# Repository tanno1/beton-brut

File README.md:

### beton brut
### noah tanner
### summer 2024

beton brut is a brutalist inspired, 66pc keyboard based on the Leopold FC660M layout complete with a concrete case designed from scratch and built by noah tanner.
this readme file will outline the design and build process, while highlighting technical details in a way that hopefully is not too boring. if i do this all correctly, this document should be guiding and inspiring enough for people to embark on their own rewarding journey of making a keyboard from scratch (it is so satisfying typing this document on my own keyboard).

#### table of contents
1. [preliminary-design](#preliminary-design)
2. [electronics](#electronics)
3. [firmware](#firmware)
4. [case](#case)
5. [other-items](#other-items)
7. [build](#build)
8. [reflection](#reflection)
9. [license](#license)
10. [acknowledgements](#acknowledegments)

### preliminary-design
the motivation for this project was enhance my electronics and product design skills by designing an aesthetic keyboard that pulled visual influence from 1950s [brutalist](https://en.wikipedia.org/wiki/Brutalist_architecture) architecture. starting with youtube videos and some internet browsing, i was able to breakdown the keyboard build process into a few parts: electronics, case, keys, and then the inbetween "joinery" stuff like gaskets and peripheral items to secure the pcb in the case. i have a background in mechanical engineering so i was familiar with micro controllers and electronics, but i had not designed a pcb before so i knew that would be the most difficult part of the project. 

for the keyboard design and layout, i went on keyboard layout editor ([kle](http://www.keyboard-layout-editor.com/())) and searched through default layouts. i was really hooked by the layout of the leopold fc660 with the two offset keys and the compact layout wihtout sacrificing the arrow keys. since it was going to be my first full custom pcb, i decided to move forward with the leopold layout rather than trying to create a new one for myself. as for the look of the case, i wanted it to be a simple slab of concrete, very minimally finished and decorated in order to align with the principles of brtualism. i chose a 6 degree angle to keep the case relatively flat, but still offer me some angle to align with my natural wrist positioning.

### electronics
i used kicad for pcb design. it is a great product and extremely easy to get familiar with. for the first iteration, i referenced a [video](https://www.youtube.com/watch?v=iznKltVU1yw) by noah kiser on youtube that showed the process of creating a keyboard pcb that used a teensy microcontroller unit and through hole diodes. noah detailed all of the footprints that would be used in keyboard making and where to find them online which was really helpful. that guide worked great up until the point where i started routing my martrix to the teensy and realized that the 18 gpio pinouts on the teensy were not enough to meet my 20 needed (5 rows and 15 columns). a quick reddit post about my dilemma and a few hour wait brought me into contact with markus knutsson ([github](https://github.com/TweetyDaBird/)). markus recommended that i alter my matrix layout in a way that would work, but would be quite ugly, or alternatively replace the teensy with an rp2040. from the start of the project, i was aware of using an on board mcu, but i was too nervous to setup the peripheral devices and risk messing it up. after reading marcus' reply, i checked online about the rp2040 mcu and decided to give it a try. having used raspberry pi devices in the past, i know their documentation is great, and that proved to be the case with the rp2040 as well. the [datasheet](https://datasheets.raspberrypi.com/rp2040/rp2040-datasheet.pdf?_gl=1*18x0kee*_ga*MTU3NjQ0Mzc0Ny4xNzI0NTQ0NTU5*_ga_22FD70LWDS*MTcyNDU0NDU1OS4xLjEuMTcyNDU0NDU4MC4wLjAuMA..) and the [hardware-design-with-the-rp2040](https://datasheets.raspberrypi.com/rp2040/hardware-design-with-rp2040.pdf?_gl=1*18x0kee*_ga*MTU3NjQ0Mzc0Ny4xNzI0NTQ0NTU5*_ga_22FD70LWDS*MTcyNDU0NDU1OS4xLjEuMTcyNDU0NDU4MC4wLjAuMA..) were all i needed to set up the rp2040 on my pcb. the hardware design manual had a very well written out process for setting up the rp2040 with qpsi flash storage, a usb port, a crystal, and information on sizing capacitors and resistors as well. thank you so much raspberry pi for making a datasheet that 1. doesn't suck, and 2. is't boring to read. 

after reading through these two manuals and with a few hours of work i was able to setup my first iteration of the pcb board. i was pretty hyped. i sent it over to marcus to get some feedback and he let me know that it was pretty terrible and problematic. the problems came in two forms. the first was that i routed every line to the outsides of the board, thinking that it would make sense to keep things away from the center and not crowd the board. while this worked out for the crwoding issue, it was a terrible design choice. routing traces to the edges of a board is bad for electromagnetic interference and could lead to issues with other electronics on my desk near the keyboard. the second issue with the board was that i did not use any vias. my reasoning for this came down to a lack of experience and pcb familiarity. i thought vias were a last resort thing and justified that, if i can put everything on one side, why not do that? inversely though, why not divide things on both sides of the board using vias and route N->S one side, and E->W on the other. 

building off the feedback from marcus, i started over from scratch and rerouted the whole board. as you can see in the photos, it looks so much better than the first iteration. routing across the two sides was way quicker than the first time thanks to the use of vias. after routing, i ran the kicad design rule checker (drc) and found a comically high number of warnings, 188 to be exact. luckily there were 0 errors, and the warnings were all about silkscreen overlaps. at this point i was just tidying up the loose ends. i fixed the silkscreen overlaps by moving the silkscreened component names around on the board and added a border for the board production. the 3d model looked great now, no errors, and marcus verified everything looked correct and was ready for production. 

i ordered everything off of jlpcb, and this was esaily the most confusing part of the project. jlpcb makes it really easy to go through the steps of uploading the files that you need like the gerbers, positioning, and bom. despite this, the component selection was difficult to navigate and find what piece you needed. i ended up having to reorder this a few times and ran into some errors of footprint sizing which meant i had to go back into kicad, select new footprints, and then re-export the gerbers again. luckily, the jlpcb staff is incredibly helpful and always avaiable online. no joke, they have a nigh shift team so any question i had, i would ask in the live chat and have a response in minutes. 

that wraps up the electronics.

### firmware
shoutout to [qmk](https://qmk.fm/). without them, this would not be possible. qmk makes the firmware sooo much easier, and they have extensive support for many mcus, including the rp2040. going through the qmk setup is pretty straightforward and i won't dive into it too much because i am not an expert on it. the main issue i had with qmk was the lack of documentation they had for their new config.json file. the setup through the config.json file is supposed to make the keyboard setup easier than it previously was. unfortunately, there is not a lot of good documentation about the config.json file itself and the current tutorial setup referes to the rules.mk file and the "old" way of doing things, so it got a bit tricky to navigate. regardless, the cli tool and qmk firmware as a whole are incredible projects and i cannot wait to work more with them in future keyboards. 

### case
to design the case, i needed to finalize the pcb to have information on the dimensions to build around. sticking to my original design, i made a really simple slab case in fusion 360 with a 6 degree angle. the pcb laid in side of the case, contacting with the case on only the edges of the pcb board. a tricky part of this design was going to be the usb-c cable bceause i did not want to leave the area above it exposed. to make the mold in fusion, i made another component and made a rectangular body a bit bigger than the case. aligning the bottom face of the case with a face of the new body, i then used the subtract tool to create a negative of the case. i split this negative into 4 components so that they could be 3d printed and then fastened together. i fastened them using sikaflex which was a mistake because the pieces were so tightly bound that when it was time to remove the mold, they would not budge from eachother. in short, this mold did not work. i used a grout mix for the first casting and that part worked well, but i could not get the case out of the mold when it had dried. i expected this to be somewhat of a problem, but it was much more severe than i anticipated. the case had no drafted edges, so each of the corners effectively "sucked" in the concrete. i tried using a pneumatic powered saw to cut away the sides of the case and pull it out slowly, but it ended up breaking the case. the other massive issue with this case was usb-c port design. it was an exposed hole through the wall of the case, so the mold would have concrete around it, and no easy way to remove the mold. this was not going to work and i needed a new solution. see the photos down below. 

for the second attempt, i used a cement mix instead of the grout bceause the cement would look a lot better. for the new mold design, i added filleted corners on all of the previosuly 90 degree joints, hoping that it would pop out a lot easier. i also put some draft angles in the center parts of the mold that can be seen in the photos below. for the usb-c port, i came up with a great design that left the area above the port open, and had a separate insert piece to fit over that, and rest across the board. this solved the usb-c issue and also occupied the blank space on the pcb between the main keys and the offset two piece keys. lastly, i used clamps rather than sikaflex so that when the case had dried, i could remove each quadrant with ease. despite all these changed, it was still not quite there! the case was too fragile and broke again when i was taking it out. i think this was due to the design angles again, as well as the material. the outer walls of the case were too short and did not cover the key switches as much as i wanted. the top case piece broke as well because there were too many 90 degree angles, some drafts and fillets should fix that easily. time for a third iteration.

in the third attempt, i removed the fillets and added more draft angles on every inner wall of the mold. i raised the wall height as well and was ready to go. for the third mix, i used the same cement, but added a structural adhesive to help out with the strength. after coating the mold in wd40 to help with the release, casting, and waiting, i took it apart and the case came out great! the insert piece worked great as well, but i forgot to invert the mold so that the exposed part of the cast was the piece that would be facing up in the final design. you an see this in the way that it contrasts a bit with the case in the final version, but i will keep it like that, i kind of enjoy it. for finishing, i coated the case in laquer a few times and then added a few coats of johnson paste wax. since the cement is so porous, the final result is really smooth and not sticky. i am really impressed with the finish.

### other-items
here is everything else i purchased, it is all self-explanatory:
1. [keycaps](https://www.aliexpress.us/item/3256806228987028.html?spm=a2g0o.order_list.order_list_main.5.7f441802ZPgCd5&gatewayAdapt=glo2usa)
2. [butyl](https://www.aliexpress.us/item/3256806034781549.html?spm=a2g0o.order_list.order_list_main.10.7f441802ZPgCd5&gatewayAdapt=glo2usa)
3. [usb-c](https://www.aliexpress.us/item/3256805246064043.html?spm=a2g0o.order_list.order_list_main.15.7f441802ZPgCd5&gatewayAdapt=glo2usa)
4. [stabilizers](https://www.aliexpress.us/item/3256801499984864.html?spm=a2g0o.order_list.order_list_main.20.7f441802ZPgCd5&gatewayAdapt=glo2usa)
5. [cherry-mx-black](https://www.aliexpress.us/item/3256806069646359.html?spm=a2g0o.order_list.order_list_main.25.7f441802ZPgCd5&gatewayAdapt=glo2usa)
6. [foam-pads](https://www.aliexpress.us/item/3256804440346820.html?spm=a2g0o.order_list.order_list_main.30.7f441802ZPgCd5&gatewayAdapt=glo2usa)
7. [tactile-switch](https://www.aliexpress.us/item/3256806891393231.html?spm=a2g0o.order_list.order_list_main.35.7f441802ZPgCd5&gatewayAdapt=glo2usa)

### build
when all of the items came in, i soldered the switches and buttons onto the board, making sure to put the foam patches underneath the switches. after flashing the firmware and testing the board, the rest of the assembly was pretty straightforward. throughout the case build, i had been periodically placing the pcb in the failed builds to make sure that it was sitting in the case properly. to protect the edges of the board and secure it in the case, i used butyl tape and put it on the edges of walls next to where the board sat, as well as a tiny bit underneath the board to grip it well. the one thing to note is that the final design of the top insert piece that covers the usb-c nudges up a bit too closely to the right arrow key and i had to sandpaper it down a lot to make it fit. i doubt anyone will be replicating this build. but if one were to, this would need to be changed or sanded down again. otherwise, the build worked like a dream and the case is really solidly held together.

### reflection
i am so happy with how this build came out. i learned so much throughout this project and it would not have been possible without marcus knutsson, noah kiser, raspberry pi, the kicad forum, and my father. reflecting upon this project, i think the biggest success was the pcb design itself, but the case was relatively rudimentary and would have benefitted from some stand off mounting posts, and more professional mounting hardware than just the butyl tape. that being said, i would need to include screw post holes on the pcb as well, something i did not even vaguely consider at the time. once again, massive shout out to everyone that helped me, if you have read through this far, please take a minute to go check out some of their work, linked in [acknowledgements](acknowledgments). lastly, if you are building a keyboard and somehow found yourself here, feel free to contact me with any questions. it seems like a daunting task, but its fun and **extremely** rewarding and i would love to help out in the way that others helped me. 

### license
MIT License

Copyright (c) [2024] [noah tanner]

Permission is hereby granted, free of charge, to any person obtaining a copy
of this software and associated documentation files (the "Software"), to deal
in the Software without restriction, including without limitation the rights
to use, copy, modify, merge, publish, distribute, sublicense, and/or sell
copies of the Software, and to permit persons to whom the Software is
furnished to do so, subject to the following conditions:

The above copyright notice and this permission notice shall be included in all
copies or substantial portions of the Software.

THE SOFTWARE IS PROVIDED "AS IS", WITHOUT WARRANTY OF ANY KIND, EXPRESS OR
IMPLIED, INCLUDING BUT NOT LIMITED TO THE WARRANTIES OF MERCHANTABILITY,
FITNESS FOR A PARTICULAR PURPOSE AND NONINFRINGEMENT. IN NO EVENT SHALL THE
AUTHORS OR COPYRIGHT HOLDERS BE LIABLE FOR ANY CLAIM, DAMAGES OR OTHER
LIABILITY, WHETHER IN AN ACTION OF CONTRACT, TORT OR OTHERWISE, ARISING FROM,
OUT OF OR IN CONNECTION WITH THE SOFTWARE OR THE USE OR OTHER DEALINGS IN THE
SOFTWARE.

### acknowledegments
- [marcus knutsson](https://github.com/TweetyDaBird/)
- [noah kiser](https://www.youtube.com/watch?v=iznKltVU1yw)
- [qmk](https://qmk.fm/)

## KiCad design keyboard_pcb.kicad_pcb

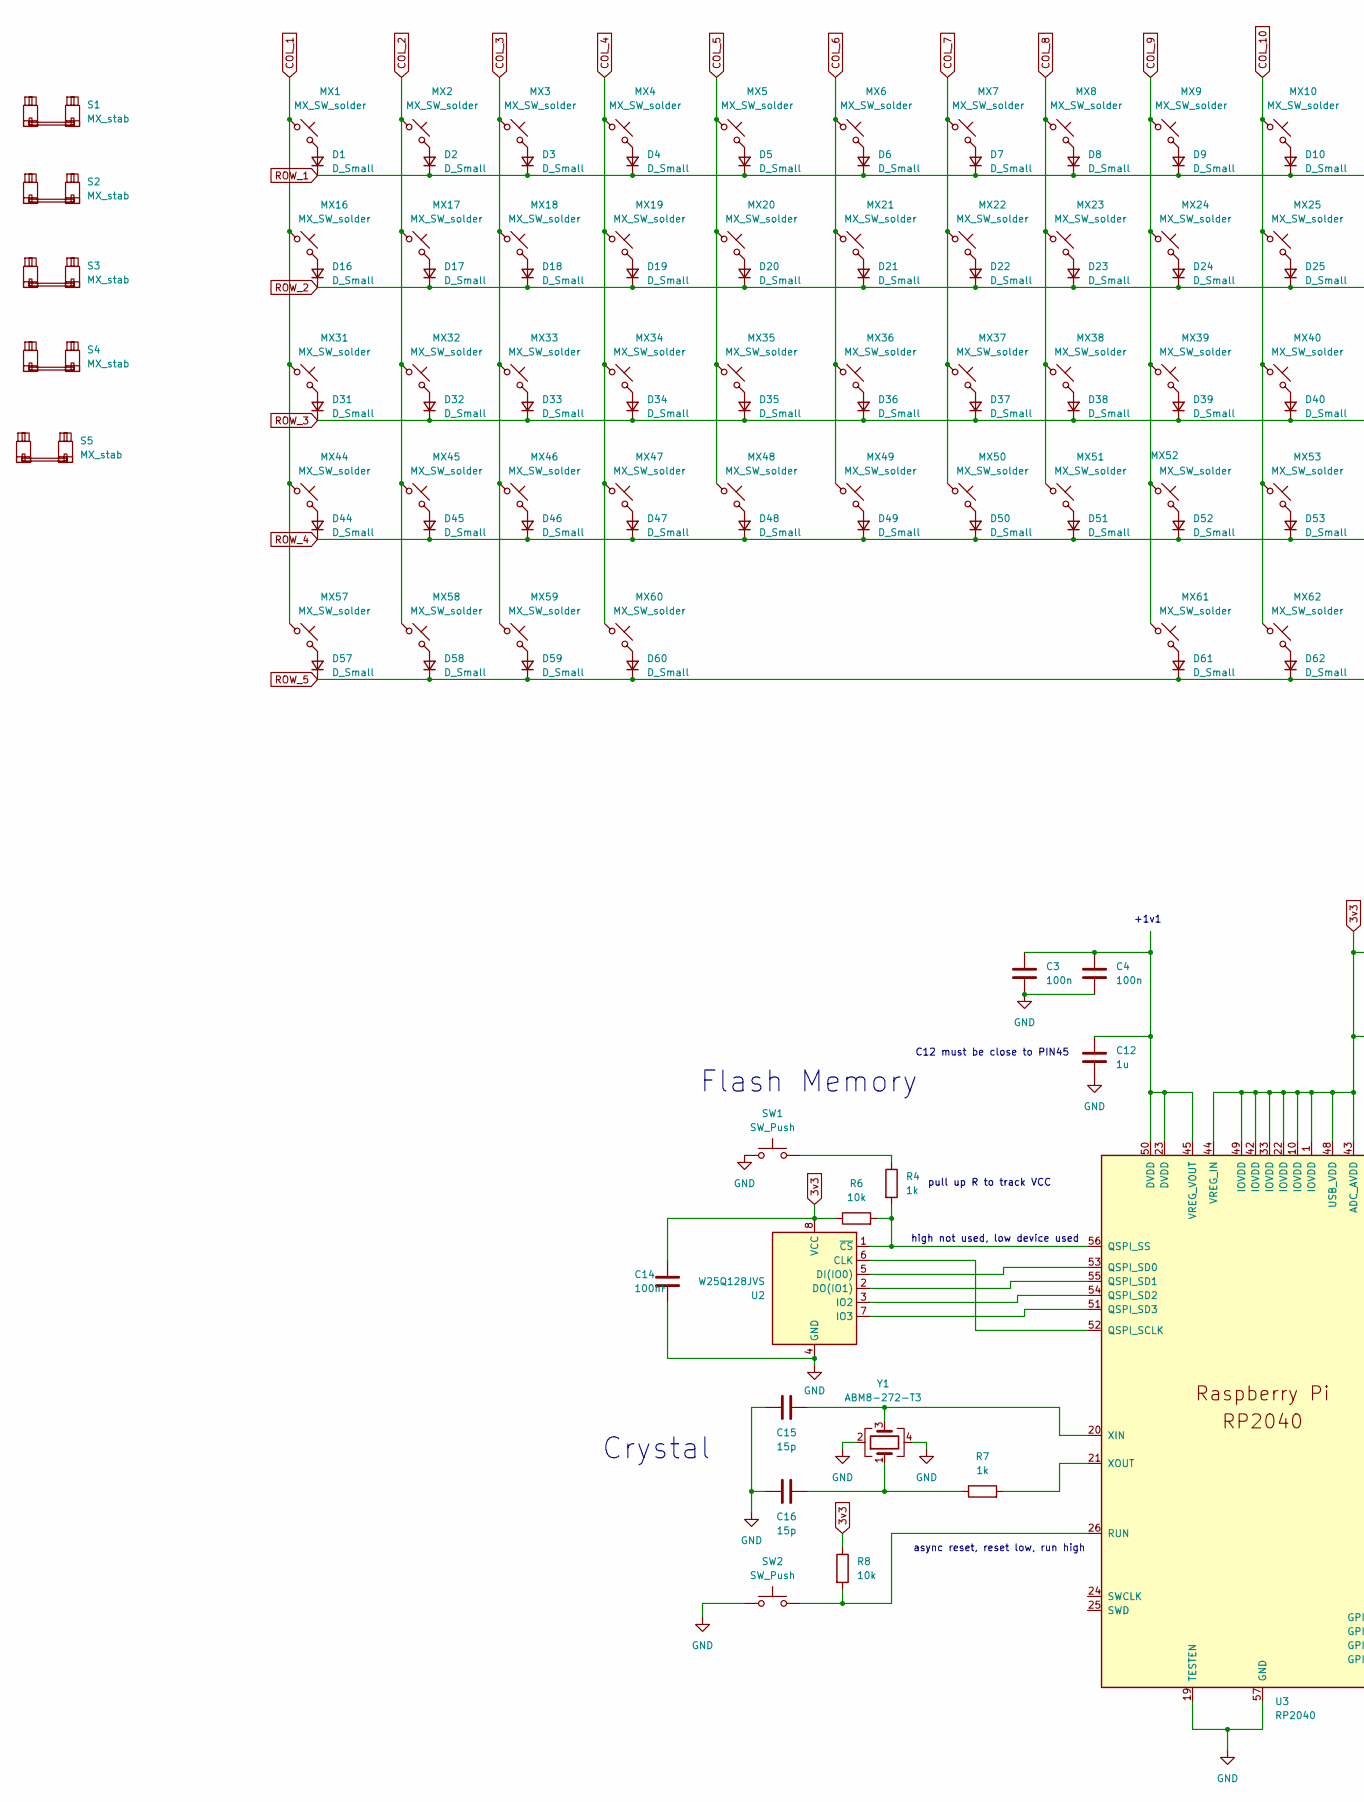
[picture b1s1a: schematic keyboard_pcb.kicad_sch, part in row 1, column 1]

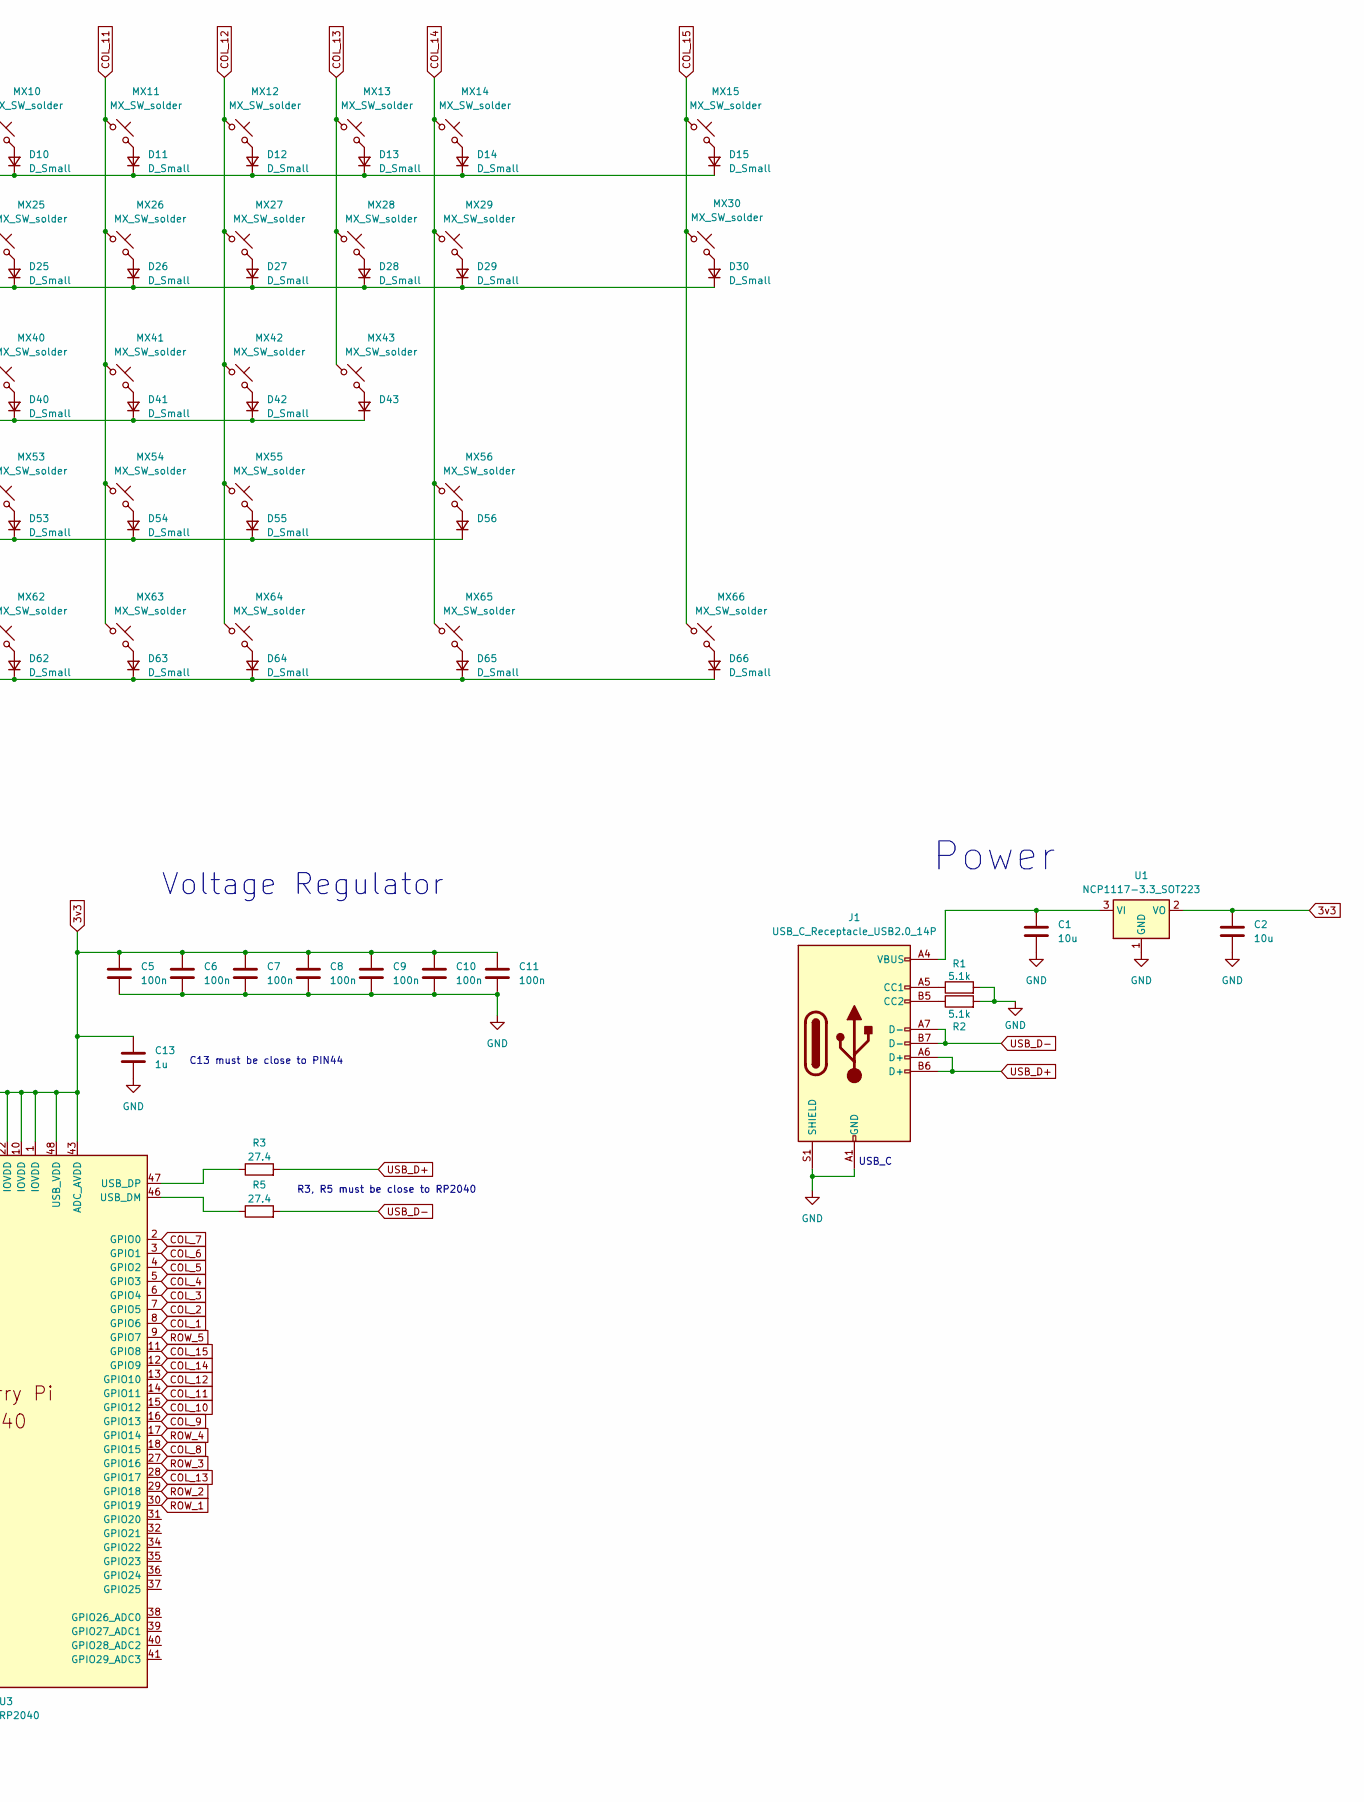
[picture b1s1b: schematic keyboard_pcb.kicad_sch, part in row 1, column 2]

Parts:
C1, C2: 10u; C_0402_1005Metric
C3, C4, C5, C6, C7, C8, C9, C10, C11: 100n; C_0402_1005Metric
C12, C13: 1u; C_0402_1005Metric
C14: 100nF; C_0402_1005Metric
C15, C16: 15p; C_0402_1005Metric
D1, D2, D3, D4, D5, D6, D7, D8, D9, D10, D11, D12, D13, D14, D15, D16, D17, D18, D19, D20, D21, D22, D23, D24, D25, D26, D27, D28, D29, D30, D31, D32, D33, D34, D35, D36, D37, D38, D39, D40, D41, D42, D43, D44, D45, D46, D47, D48, D49, D50, D51, D52, D53, D54, D55, D56, D57, D58, D59, D60, D61, D62, D63, D64, D65, D66: D_Small; D_SOD-123
J1: USB_C_Receptacle_USB2.0_14P; USB_C_Receptacle_HRO_TYPE-C-31-M-12
MX1, MX2, MX3, MX4, MX5, MX6, MX7, MX8, MX9, MX10, MX11, MX12, MX13, MX14, MX15, MX17, MX18, MX19, MX20, MX21, MX22, MX23, MX24, MX25, MX26, MX27, MX28, MX30, MX32, MX33, MX34, MX35, MX36, MX37, MX38, MX39, MX40, MX41, MX42, MX43, MX44, MX45, MX46, MX47, MX48, MX49, MX50, MX51, MX52, MX53, MX54, MX55, MX56, MX58, MX60, MX64, MX65, MX66: MX_SW_solder; SW_MX_1u
MX16, MX29: MX_SW_solder; SW_MX_1.5u
MX31: MX_SW_solder; SW_MX_1.75u
MX57, MX59, MX61, MX62, MX63: MX_SW_solder; SW_MX_1.25u
R1, R2: 5.1k; R_0402_1005Metric
R3, R5: 27.4; R_0402_1005Metric
R4, R7: 1k; R_0402_1005Metric
R6, R8: 10k; R_0402_1005Metric
S1: MX_stab; STAB_MX_2u
S2, S3, S4: MX_stab; STAB_MX_2.25u
S5: MX_stab; STAB_MX_P_6.25u
SW1, SW2: SW_Push; SW_PUSH_6mm
U1: NCP1117-3.3_SOT223; SOT-223-3_TabPin2
U2: W25Q128JVS; SOIC-8_5.23x5.23mm_P1.27mm
U3: RP2040; RP2040-QFN-56
Y1: ABM8-272-T3; Crystal_SMD_Abracon_ABM8G-4Pin_3.2x2.5mm

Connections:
3v3: C2.1, C5.1, C6.1, C7.1, C8.1, C9.1, C10.1, C11.1, C13.1, C14.1, R6.1, R8.1, U1.2 (VO), U2.8 (VCC), U3.1 (IOVDD), U3.10 (IOVDD), U3.22 (IOVDD), U3.33 (IOVDD), U3.42 (IOVDD), U3.43 (ADC_AVDD), U3.44 (VREG_IN), U3.48 (USB_VDD), U3.49 (IOVDD)
COL_1: MX1.1, MX16.1, MX31.1, MX44.1, MX57.1, U3.8 (GPIO6)
COL_2: MX2.1, MX17.1, MX32.1, MX45.1, MX58.1, U3.7 (GPIO5)
COL_3: MX3.1, MX18.1, MX33.1, MX46.1, MX59.1, U3.6 (GPIO4)
COL_4: MX4.1, MX19.1, MX34.1, MX47.1, MX60.1, U3.5 (GPIO3)
COL_5: MX5.1, MX20.1, MX35.1, MX48.1, U3.4 (GPIO2)
COL_6: MX6.1, MX21.1, MX36.1, MX49.1, U3.3 (GPIO1)
COL_7: MX7.1, MX22.1, MX37.1, MX50.1, U3.2 (GPIO0)
COL_8: MX8.1, MX23.1, MX38.1, MX51.1, U3.18 (GPIO15)
COL_9: MX9.1, MX24.1, MX39.1, MX52.1, MX61.1, U3.16 (GPIO13)
COL_10: MX10.1, MX25.1, MX40.1, MX53.1, MX62.1, U3.15 (GPIO12)
COL_11: MX11.1, MX26.1, MX41.1, MX54.1, MX63.1, U3.14 (GPIO11)
COL_12: MX12.1, MX27.1, MX42.1, MX55.1, MX64.1, U3.13 (GPIO10)
COL_13: MX13.1, MX28.1, MX43.1, U3.28 (GPIO17)
COL_14: MX14.1, MX29.1, MX56.1, MX65.1, U3.12 (GPIO9)
COL_15: MX15.1, MX30.1, MX66.1, U3.11 (GPIO8)
GND: C1.2, C2.2, C3.2, C4.2, C5.2, C6.2, C7.2, C8.2, C9.2, C10.2, C11.2, C12.2, C13.2, C14.2, C15.1, C16.1, J1.A1 (GND), J1.A12 (GND), J1.B1 (GND), J1.B12 (GND), J1.S1 (SHIELD), R1.2, R2.2, SW1.1, SW2.1, U1.1 (GND), U2.4 (GND), U3.19 (TESTEN), U3.57 (GND), Y1.2, Y1.4
unnamed: C16.2, R7.1, Y1.1
unnamed: D1.2 (A), MX1.2
unnamed: D2.2 (A), MX2.2
unnamed: D3.2 (A), MX3.2
unnamed: D4.2 (A), MX4.2
unnamed: D5.2 (A), MX5.2
unnamed: D6.2 (A), MX6.2
unnamed: D7.2 (A), MX7.2
unnamed: D8.2 (A), MX8.2
unnamed: D9.2 (A), MX9.2
unnamed: D10.2 (A), MX10.2
unnamed: D11.2 (A), MX11.2
unnamed: D12.2 (A), MX12.2
unnamed: D13.2 (A), MX13.2
unnamed: D14.2 (A), MX14.2
unnamed: D15.2 (A), MX15.2
unnamed: D16.2 (A), MX16.2
unnamed: D17.2 (A), MX17.2
unnamed: D18.2 (A), MX18.2
unnamed: D19.2 (A), MX19.2
unnamed: D20.2 (A), MX20.2
unnamed: D21.2 (A), MX21.2
unnamed: D22.2 (A), MX22.2
unnamed: D23.2 (A), MX23.2
unnamed: D24.2 (A), MX24.2
unnamed: D25.2 (A), MX25.2
unnamed: D26.2 (A), MX26.2
unnamed: D27.2 (A), MX27.2
unnamed: D28.2 (A), MX28.2
unnamed: D29.2 (A), MX29.2
unnamed: D30.2 (A), MX30.2
unnamed: D31.2 (A), MX31.2
unnamed: D32.2 (A), MX32.2
unnamed: D33.2 (A), MX33.2
unnamed: D34.2 (A), MX34.2
unnamed: D35.2 (A), MX35.2
unnamed: D36.2 (A), MX36.2
unnamed: D37.2 (A), MX37.2
unnamed: D38.2 (A), MX38.2
unnamed: D39.2 (A), MX39.2
unnamed: D40.2 (A), MX40.2
unnamed: D41.2 (A), MX41.2
unnamed: D42.2 (A), MX42.2
unnamed: D43.2 (A), MX43.2
unnamed: D44.2 (A), MX44.2
unnamed: D45.2 (A), MX45.2
unnamed: D46.2 (A), MX46.2
unnamed: D47.2 (A), MX47.2
unnamed: D48.2 (A), MX48.2
unnamed: D49.2 (A), MX49.2
unnamed: D50.2 (A), MX50.2
unnamed: D51.2 (A), MX51.2
unnamed: D52.2 (A), MX52.2
unnamed: D53.2 (A), MX53.2
unnamed: D54.2 (A), MX54.2
unnamed: D55.2 (A), MX55.2
unnamed: D56.2 (A), MX56.2
unnamed: D57.2 (A), MX57.2
unnamed: D58.2 (A), MX58.2
unnamed: D59.2 (A), MX59.2
unnamed: D60.2 (A), MX60.2
unnamed: D61.2 (A), MX61.2
unnamed: D62.2 (A), MX62.2
unnamed: D63.2 (A), MX63.2
unnamed: D64.2 (A), MX64.2
unnamed: D65.2 (A), MX65.2
unnamed: D66.2 (A), MX66.2
unnamed: J1.A5 (CC1), R1.1
unnamed: J1.B5 (CC2), R2.1
unnamed: R4.1, SW1.2
unnamed: C1.1, J1.A4 (VBUS), J1.A9 (VBUS), J1.B4 (VBUS), J1.B9 (VBUS), U1.3 (VI)
unnamed: U2.6 (CLK), U3.52 (QSPI_SCLK)
unnamed: U2.5 (DI(IO0)), U3.53 (QSPI_SD0)
unnamed: U2.2 (DO(IO1)), U3.55 (QSPI_SD1)
unnamed: U2.3 (IO2), U3.54 (QSPI_SD2)
unnamed: U2.7 (IO3), U3.51 (QSPI_SD3)
unnamed: R4.2, R6.2, U2.1 (~CS), U3.56 (QSPI_SS)
unnamed: R8.2, SW2.2, U3.26 (RUN)
unnamed: R5.1, U3.46 (USB_DM)
unnamed: R3.1, U3.47 (USB_DP)
unnamed: C3.1, C4.1, C12.1, U3.23 (DVDD), U3.45 (VREG_VOUT), U3.50 (DVDD)
unnamed: C15.2, U3.20 (XIN), Y1.3
unnamed: R7.2, U3.21 (XOUT)
ROW_1: D1.1 (K), D2.1 (K), D3.1 (K), D4.1 (K), D5.1 (K), D6.1 (K), D7.1 (K), D8.1 (K), D9.1 (K), D10.1 (K), D11.1 (K), D12.1 (K), D13.1 (K), D14.1 (K), D15.1 (K), U3.30 (GPIO19)
ROW_2: D16.1 (K), D17.1 (K), D18.1 (K), D19.1 (K), D20.1 (K), D21.1 (K), D22.1 (K), D23.1 (K), D24.1 (K), D25.1 (K), D26.1 (K), D27.1 (K), D28.1 (K), D29.1 (K), D30.1 (K), U3.29 (GPIO18)
ROW_3: D31.1 (K), D32.1 (K), D33.1 (K), D34.1 (K), D35.1 (K), D36.1 (K), D37.1 (K), D38.1 (K), D39.1 (K), D40.1 (K), D41.1 (K), D42.1 (K), D43.1 (K), U3.27 (GPIO16)
ROW_4: D44.1 (K), D45.1 (K), D46.1 (K), D47.1 (K), D48.1 (K), D49.1 (K), D50.1 (K), D51.1 (K), D52.1 (K), D53.1 (K), D54.1 (K), D55.1 (K), D56.1 (K), U3.17 (GPIO14)
ROW_5: D57.1 (K), D58.1 (K), D59.1 (K), D60.1 (K), D61.1 (K), D62.1 (K), D63.1 (K), D64.1 (K), D65.1 (K), D66.1 (K), U3.9 (GPIO7)
USB_D+: J1.A6 (D+), J1.B6 (D+), R3.2
USB_D-: J1.A7 (D-), J1.B7 (D-), R5.2

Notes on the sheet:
+1v1
Voltage Regulator
pull up R to track VCC
USB_C
high not used, low device used
Flash Memory
C12 must be close to PIN45
async reset, reset low, run high
Crystal
C13 must be close to PIN44
Power
R3, R5 must be close to RP2040

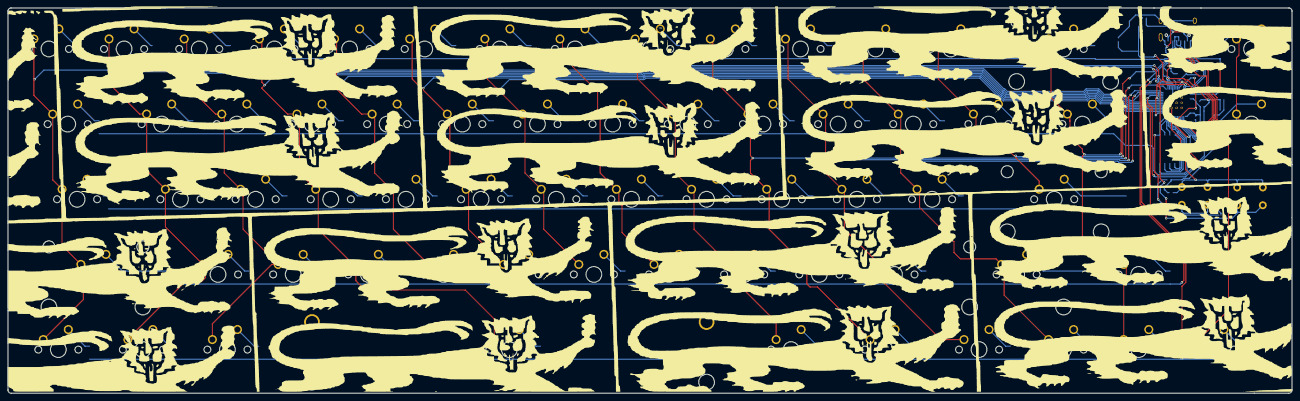
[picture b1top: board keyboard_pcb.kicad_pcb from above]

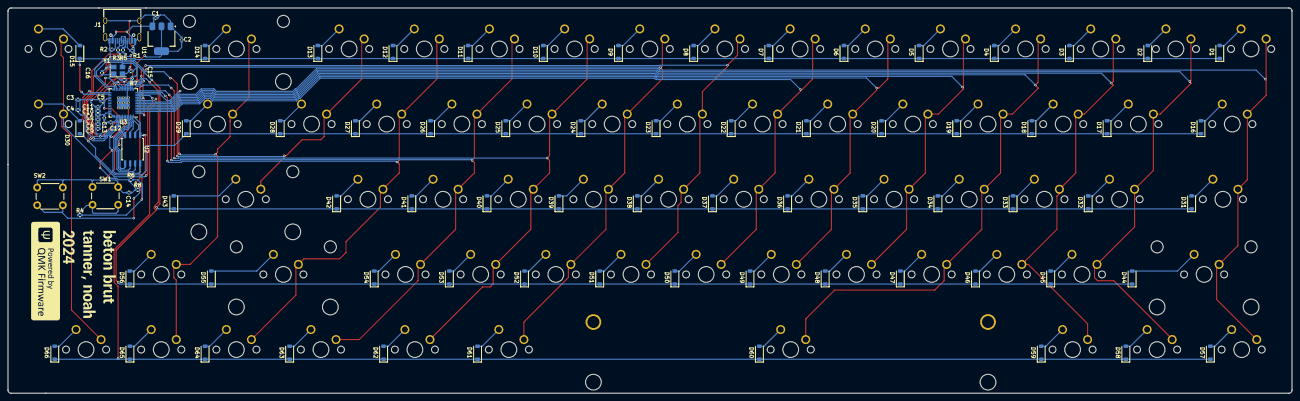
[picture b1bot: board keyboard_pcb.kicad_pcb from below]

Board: 2 copper layers, 325.4 x 97.6 mm, 168 parts (97 on the bottom side), 107 nets.

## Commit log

2024-06-05 updates, edge cuts
2024-06-12 cleaned up w/ .gitignore
2024-06-13 updated file structure ish
2024-06-18 JLPCB order placed today
2024-06-21 reordered, x3, hopefully final production
2024-08-25 molds, gerbs, pos, everything ready to order beton brut
2024-08-25 Update README.md
    - TODO: add images, add firmware, db check gerbs & fusion files fully updated
2024-08-26 firmware binaries added, used .uf2 and qmk flasher
2024-08-26 final result photos
2024-08-26 Rename IMG_2801.jpg to fullframe.jpg
2024-08-26 Rename IMG_2807.jpg to usbc.jpg
2024-08-26 Rename IMG_2803.jpg to closeleft.jpg
2024-08-26 Rename IMG_2802.jpg to closeright.jpg
